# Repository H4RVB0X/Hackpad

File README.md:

# Macropad

Macropad is a 6 key pad with a rotary encoder, an OLED display and 12 LED's. It uses KMK firmware.

It is inspired by the Hackpad YSWS (which has now ended so it is a now a hackpad blueprint)

## Features
- 3D printed custom case that is angled towards the user for easier use.
- 6 MX switches.
- 12 RGB LED's.
- A rotary encoder.
- A 128x32 OLED display.

## CAD Model for Case
It is screwed in using 3 M3 bolts and heatset inserts. It has a 10 degree tilt.

It is all one complete part with an open top to showcase the pcb and components.

Made in Solidworks.

## PCB
My PCB was designed in KiCad.

It was a challenge trying to route it all as I've never created a PCB before so ignore the messy wiring.

## Firmware Overview
It uses KMK firmware and may in the future be upgraded to QMK if I learn how to use it.

- The rotary encoder changes volume and is pressed to change layer.
- The 6 keys currently are assigned differently for each layer - Base (Gaming), Function, Media
- The OLED just tells you what layer your on and will in future have pictures or custom icons on there - maybe even temps if I can get that to work

## BOM

- 6x Cherry MX Switches
- 6x DSA Keycaps
- 3x M3x5x4 Heatset inserts
- 3x M3x16mm SHCS Bolts
- 6x 1N4148 DO-35 Diodes
- 12x WS2812B LEDs
- 1x 0.91" 128x32 OLED Display
- 1x EC11 Rotary Encoder
- 1x XIAO RP2040
- 1x Case (3D PrinteD)

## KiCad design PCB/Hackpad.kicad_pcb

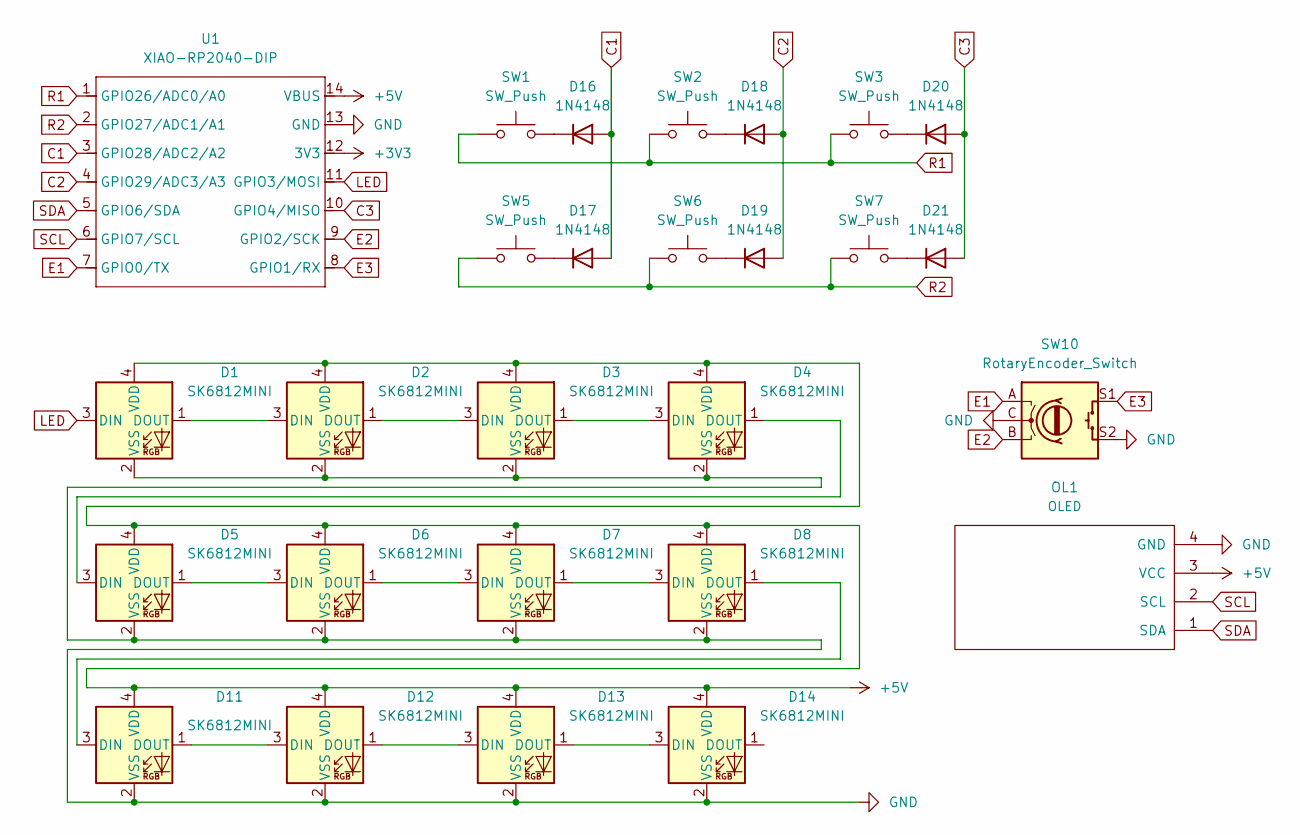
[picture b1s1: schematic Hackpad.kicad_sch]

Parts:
D1, D2, D3, D4, D5, D6, D7, D8, D11, D12, D13, D14: SK6812MINI; LED_SK6812MINI_PLCC4_3.5x3.5mm_P1.75mm
D16, D17, D18, D19, D20, D21: 1N4148; D_DO-35_SOD27_P7.62mm_Horizontal
OL1: OLED; SSD1306-0.91-OLED-4pin-128x32
SW1, SW2, SW3, SW5, SW6, SW7: SW_Push; SW_Cherry_MX_1.00u_PCB
SW10: RotaryEncoder_Switch; RotaryEncoder_Alps_EC11E-Switch_Vertical_H20mm
U1: XIAO-RP2040-DIP

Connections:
+3V3: U1.12 (3V3)
+5V: D1.4 (VDD), D2.4 (VDD), D3.4 (VDD), D4.4 (VDD), D5.4 (VDD), D6.4 (VDD), D7.4 (VDD), D8.4 (VDD), D11.4 (VDD), D12.4 (VDD), D13.4 (VDD), D14.4 (VDD), OL1.3 (VCC), U1.14 (VBUS)
C1: D16.2 (A), D17.2 (A), U1.3 (GPIO28/ADC2/A2)
C2: D18.2 (A), D19.2 (A), U1.4 (GPIO29/ADC3/A3)
C3: D20.2 (A), D21.2 (A), U1.10 (GPIO4/MISO)
E1: SW10.A, U1.7 (GPIO0/TX)
E2: SW10.B, U1.9 (GPIO2/SCK)
E3: SW10.S1, U1.8 (GPIO1/RX)
GND: D1.2 (VSS), D2.2 (VSS), D3.2 (VSS), D4.2 (VSS), D5.2 (VSS), D6.2 (VSS), D7.2 (VSS), D8.2 (VSS), D11.2 (VSS), D12.2 (VSS), D13.2 (VSS), D14.2 (VSS), OL1.4 (GND), SW10.C, SW10.S2, U1.13 (GND)
LED: D1.3 (DIN), U1.11 (GPIO3/MOSI)
unnamed: D1.1 (DOUT), D2.3 (DIN)
unnamed: D2.1 (DOUT), D3.3 (DIN)
unnamed: D3.1 (DOUT), D4.3 (DIN)
unnamed: D4.1 (DOUT), D5.3 (DIN)
unnamed: D5.1 (DOUT), D6.3 (DIN)
unnamed: D6.1 (DOUT), D7.3 (DIN)
unnamed: D7.1 (DOUT), D8.3 (DIN)
unnamed: D8.1 (DOUT), D11.3 (DIN)
unnamed: D11.1 (DOUT), D12.3 (DIN)
unnamed: D12.1 (DOUT), D13.3 (DIN)
unnamed: D13.1 (DOUT), D14.3 (DIN)
unnamed: D16.1 (K), SW1.2
unnamed: D17.1 (K), SW5.2
unnamed: D18.1 (K), SW2.2
unnamed: D19.1 (K), SW6.2
unnamed: D20.1 (K), SW3.2
unnamed: D21.1 (K), SW7.2
R1: SW1.1, SW2.1, SW3.1, U1.1 (GPIO26/ADC0/A0)
R2: SW5.1, SW6.1, SW7.1, U1.2 (GPIO27/ADC1/A1)
SCL: OL1.2 (SCL), U1.6 (GPIO7/SCL)
SDA: OL1.1 (SDA), U1.5 (GPIO6/SDA)

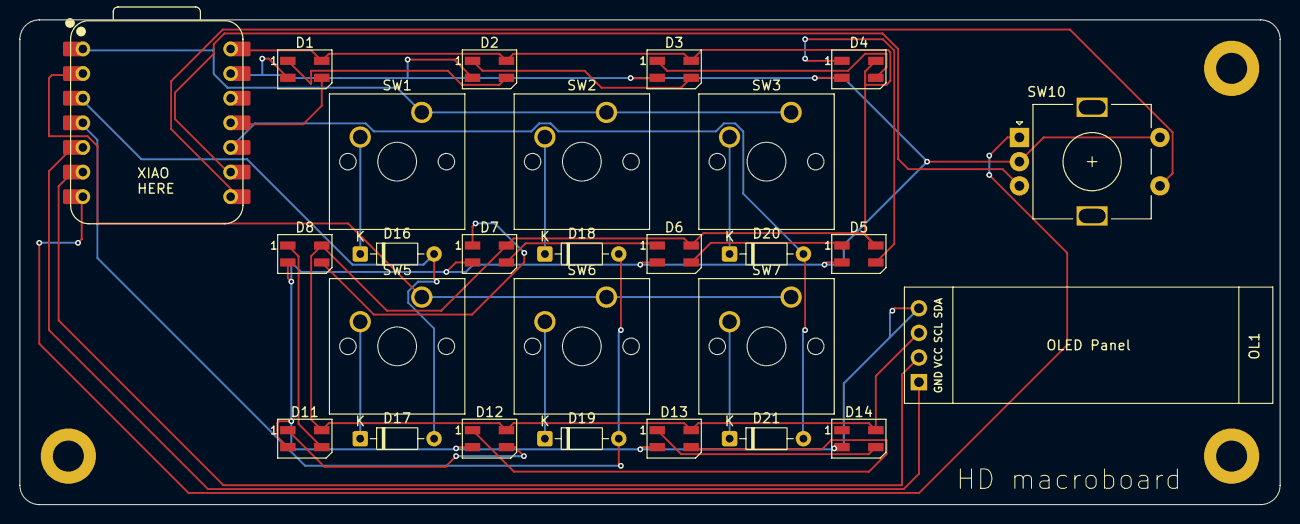
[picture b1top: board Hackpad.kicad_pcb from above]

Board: 2 copper layers, 130.0 x 50.0 mm, 27 parts (0 on the bottom side), 30 nets.

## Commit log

2025-10-28 Enhance README with features and technical details
    Expanded the README.md with detailed features, CAD model, PCB design, firmware overview, and BOM.
2025-10-28 firmware added
